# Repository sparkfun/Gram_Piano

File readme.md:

**NOTE:** *This product has been retired from our catalog. If you are looking for more up-to-date info, please check out some of these resources to see how other users are still hacking and improving on this product.*

* *[SparkFun Forum](https://forum.sparkfun.com/)*
* *[IRC Channel](https://www.sparkfun.com/news/263)*

Gram Piano
========================================

<br>
[*Gram Piano Kit (KIT-11835)*](https://www.sparkfun.com/products/11835)

The Gram Piano is a capacitive touch keyboard and soldering kit that allows you to 
create and play all the notes of the C major scale and outputs sound through a 
PCB Speaker. A different octave can be selected with the potentiometer. Pressing
the on board button will start/stop playing a melody. Feel free to adapt the keys to
play other notes/scales/melodies or perform tasks as you see fit.

This board was created in Eagle v6.0.5, this firmware was created in Arduino v1.5.2

Repository Contents
-------------------

* **/Firmware** - Firmware the board ships with.
* **/Hardware** - All Eagle design files (.brd, .sch, .STL)
* **/Production** - Test bed files and production panel files

Documentation
--------------
* **[Hookup Guide](https://learn.sparkfun.com/tutorials/gram-piano-assembly-guide)** - Basic hookup guide for the  Gram Piano.

Product Versions
----------------
* [KIT-11835 (RETIRED)](https://www.sparkfun.com/products/11835)

Version History
---------------
* vH10 Initial Redboards.
* vH05 Third protoboard run.
* vH04 Second protoboard run.
* vH03 First protoboard run.

License Information
-------------------
The hardware is released under [Creative Commons Share-alike 3.0](http://creativecommons.org/licenses/by-sa/3.0/).  
All code is open source so please feel free to do anything you want with it under the [Beerware license](http://en.wikipedia.org/wiki/Beerware).

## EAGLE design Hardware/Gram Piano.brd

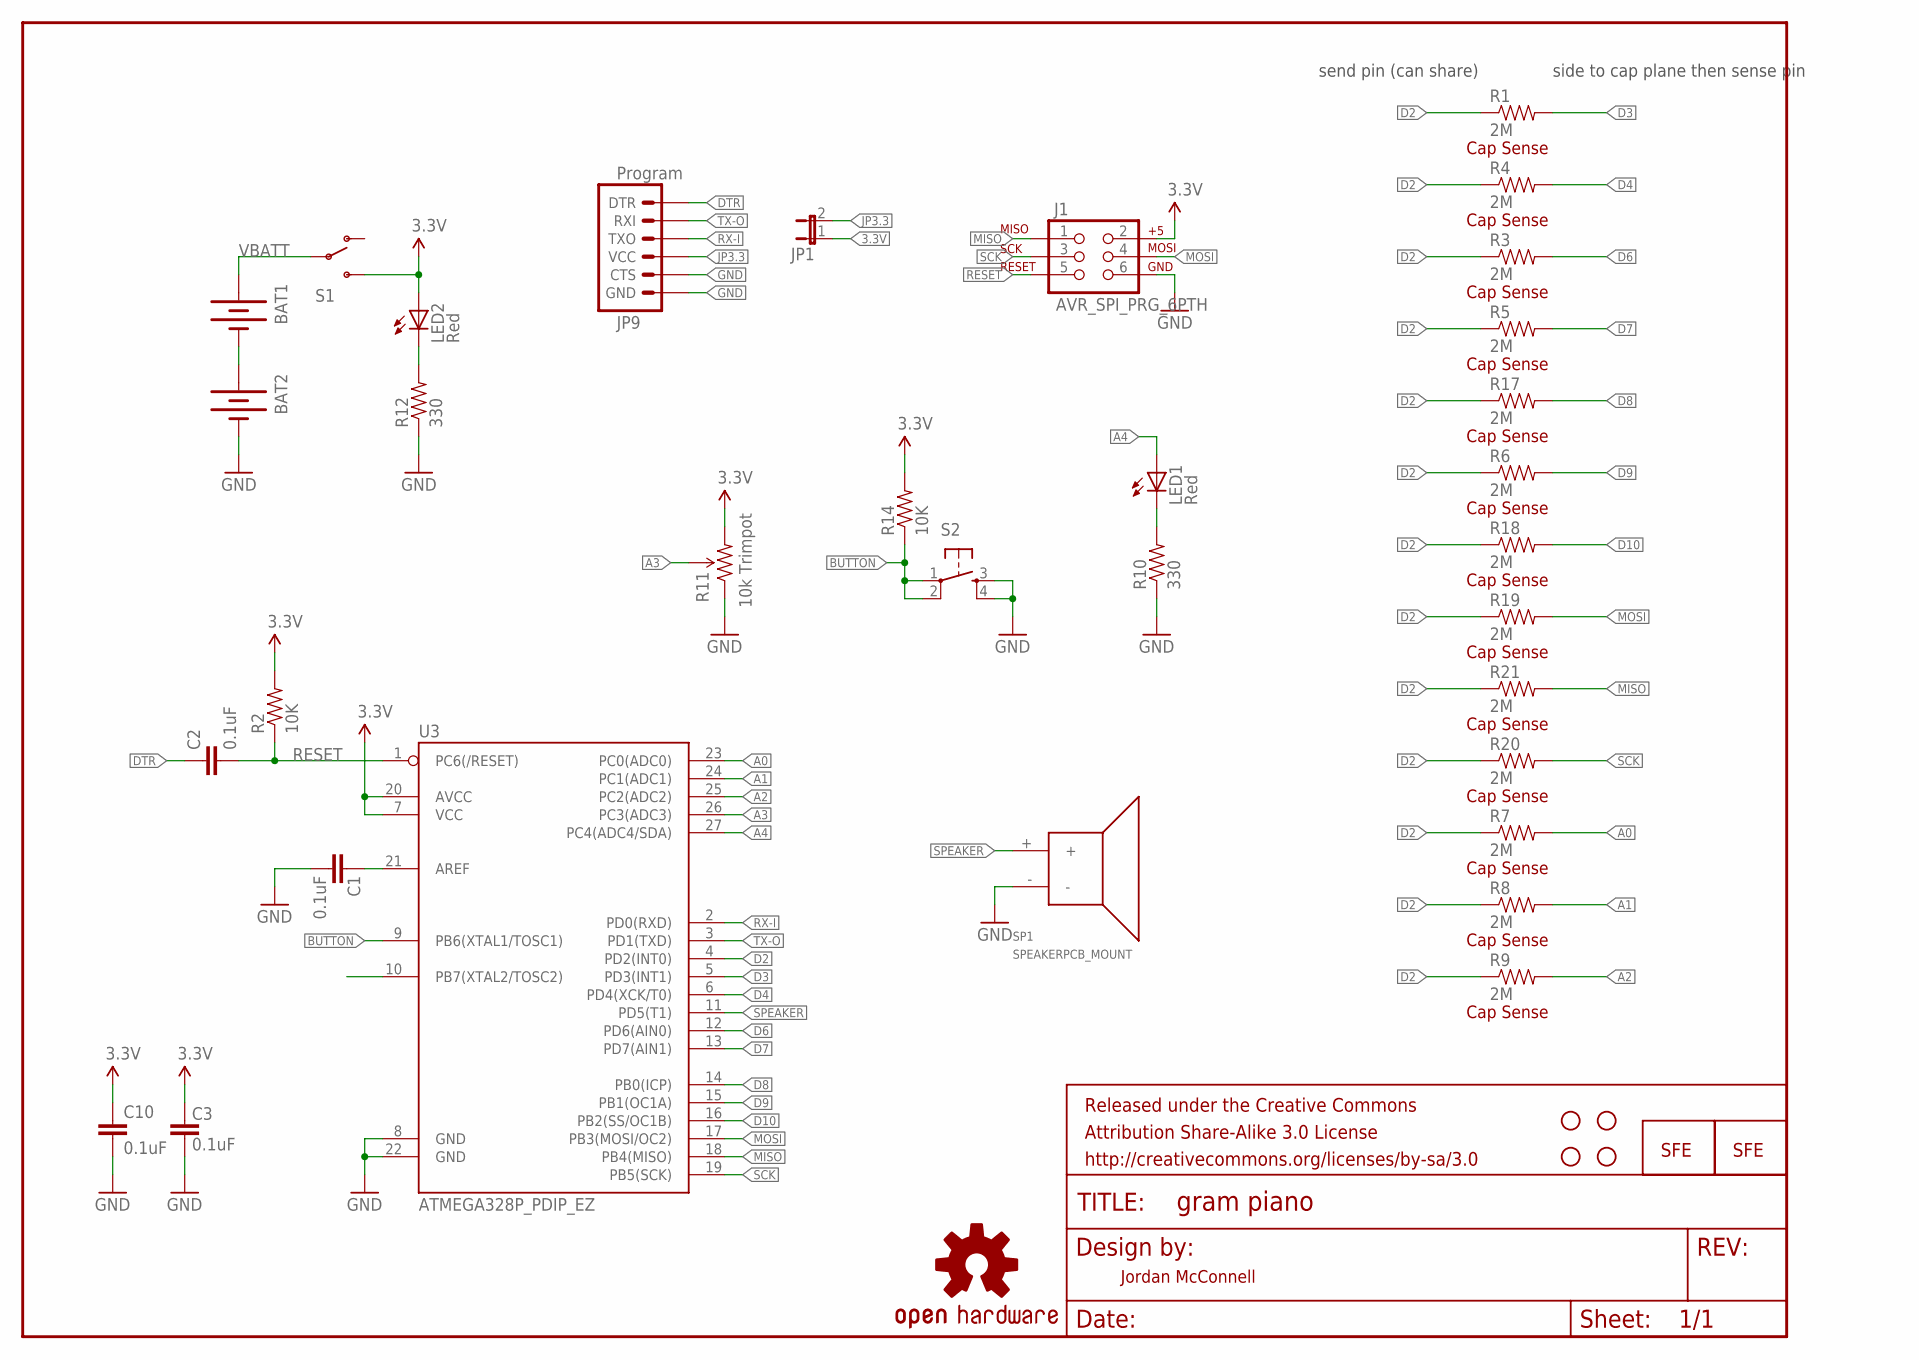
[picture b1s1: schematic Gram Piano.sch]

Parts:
BAT1, BAT2: BATTERYAA-KIT; BATTERY-AA-KIT
C1, C2, C3, C10: 0.1uF; CAP-PTH-SMALL-KIT
FRAME2: FRAME-LETTER; CREATIVE_COMMONS
J1: AVR_SPI_PRG_6PTH; 2X3
JP1: JUMPER-2SMD-NO; SJ_2S-NO
JP9: Program; 1X06-KIT
LED1, LED2: Red; LED5MM-KIT
LOGO1, LOGO2: LOGO-SFENEW; SFE-NEW-WEBLOGO
LOGO3: OSHW-LOGOM; OSHW-LOGO-M
R1, R3, R4, R5, R6, R7, R8, R9, R17, R18, R19, R20, R21: 2M; AXIAL-0.4
R2, R14: 10K; AXIAL-0.4
R10, R12: 330; AXIAL-0.4
R11: TRIMPOT-PTH-KNOB; 3386U
S1: SWITCH-SPDTKIT; SWITCH-SPDT_KIT
S2: TAC_SWITCHPTH; TACTILE-PTH
SP1: SPEAKERPCB_MOUNT; PCB_MOUNT_SPEAKER
STANDOFF1, STANDOFF2, STANDOFF3, STANDOFF4: STAND-OFF
U3: ATMEGA328P_PDIP_EZ; DIL28-EZ

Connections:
3.3V: C3.2, C10.1, J1.2, JP1.1, LED2.A, R2.P$2 (2), R11.3 (CW), R14.P$2 (2), S1.3 (S), U3.7 (VCC), U3.20 (AVCC)
A0: R7.P$2 (2), U3.23 (PC0(ADC0))
A1: R8.P$2 (2), U3.24 (PC1(ADC1))
A2: R9.P$2 (2), U3.25 (PC2(ADC2))
A3: R11.2 (WIPER), U3.26 (PC3(ADC3))
A4: LED1.A, U3.27 (PC4(ADC4/SDA))
AREF: C1.2, U3.21 (AREF)
BUTTON: R14.P$1 (1), S2.1, S2.2, U3.9 (PB6(XTAL1/TOSC1))
D2: R1.P$1 (1), R3.P$1 (1), R4.P$1 (1), R5.P$1 (1), R6.P$1 (1), R7.P$1 (1), R8.P$1 (1), R9.P$1 (1), R17.P$1 (1), R18.P$1 (1), R19.P$1 (1), R20.P$1 (1), R21.P$1 (1), U3.4 (PD2(INT0))
D3: R1.P$2 (2), U3.5 (PD3(INT1))
D4: R4.P$2 (2), U3.6 (PD4(XCK/T0))
D6: R3.P$2 (2), U3.12 (PD6(AIN0))
D7: R5.P$2 (2), U3.13 (PD7(AIN1))
D8: R17.P$2 (2), U3.14 (PB0(ICP))
D9: R6.P$2 (2), U3.15 (PB1(OC1A))
D10: R18.P$2 (2), U3.16 (PB2(SS/OC1B))
DTR: C2.1, JP9.1 (DTR)
GND: BAT2.GND@1 (-), C1.1, C3.1, C10.2, J1.6, JP9.5 (CTS), JP9.6 (GND), R10.P$1 (1), R11.1 (CCW), R12.P$1 (1), S2.3, S2.4, SP1.-, U3.8 (GND), U3.22 (GND)
JP3.3: JP1.2, JP9.4 (VCC)
MISO: J1.1, R21.P$2 (2), U3.18 (PB4(MISO))
MOSI: J1.4, R19.P$2 (2), U3.17 (PB3(MOSI/OC2))
unnamed: LED2.K (C), R12.P$2 (2)
unnamed: BAT1.GND@1 (-), BAT2.PWR@1 (+)
unnamed: LED1.K (C), R10.P$2 (2)
RESET: C2.2, J1.5, R2.P$1 (1), U3.1 (PC6(/RESET))
RX-I: JP9.3 (TXO), U3.2 (PD0(RXD))
SCK: J1.3, R20.P$2 (2), U3.19 (PB5(SCK))
SPEAKER: SP1.+, U3.11 (PD5(T1))
TX-O: JP9.2 (RXI), U3.3 (PD1(TXD))
VBATT: BAT1.PWR@1 (+), S1.2

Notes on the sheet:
Cap Sense
send pin (can share)
side to cap plane then sense pin
Jordan McConnell
10k Trimpot

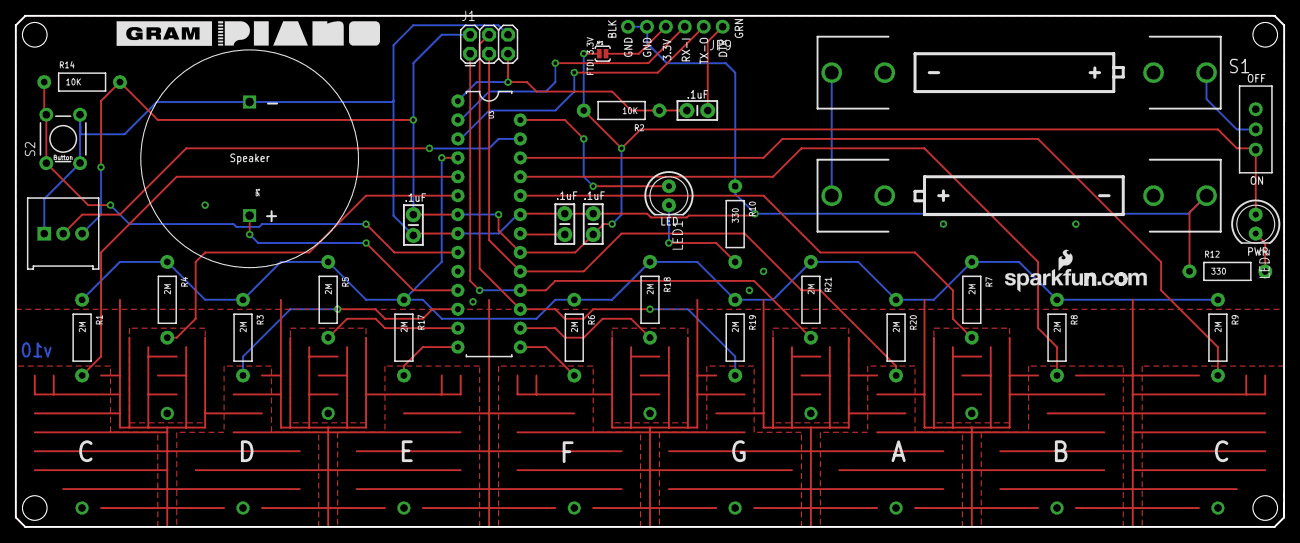
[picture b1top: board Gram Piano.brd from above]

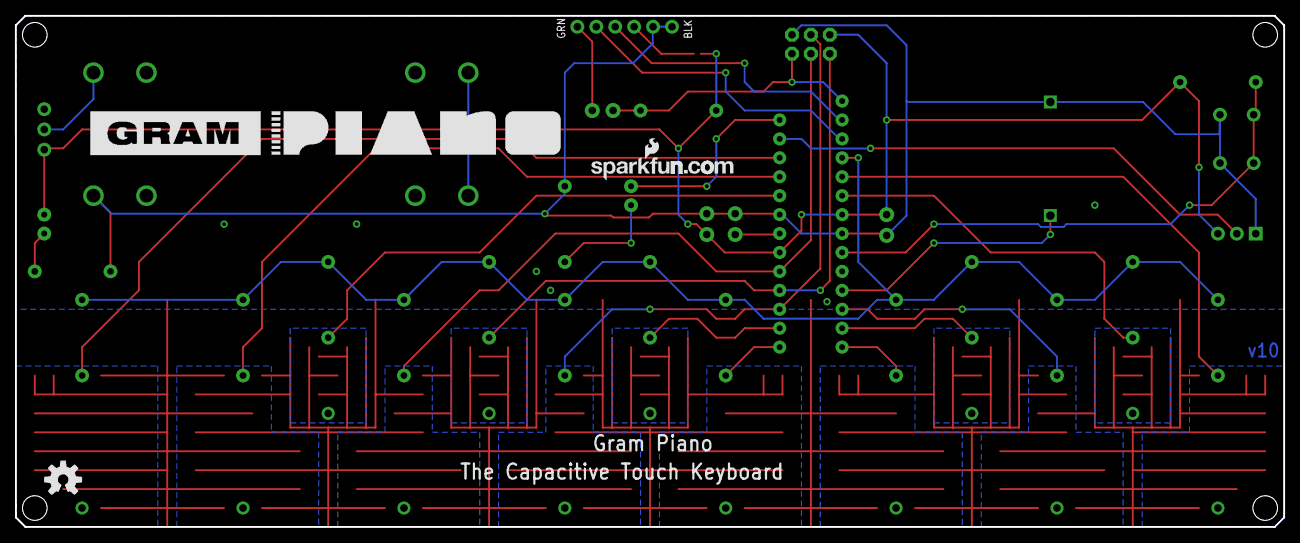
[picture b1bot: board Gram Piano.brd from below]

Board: 2 copper layers, 170.2 x 68.6 mm, 41 parts (2 on the bottom side), 30 nets.

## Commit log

2013-04-26 First prototype run, hardware v03
2013-04-29 Updated resistor packages for v03
2013-04-30 Updated inductor package for v03
2013-09-06 v04 protos, ready for review
2013-09-06 added v04 to readme
2013-09-09 v04, made changes from design review
2013-10-25 v05, next proto ready for review
2013-12-13 v10 ready for review
2013-12-16 Added silk art
2014-01-24 Added initial version of firmware
2014-03-21 Updated readme with photo/product page
2014-03-21 updated readme product link

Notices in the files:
parts and their libraries:
SparkFun-Capacitors: Licensing: CC v3.0 Share-Alike You are welcome to use this library for commercial purposes.
SparkFun-Aesthetics: Released under the Creative Commons Attribution Share-Alike 3.0 License
SparkFun-Aesthetics: Released under the Creative Commons
